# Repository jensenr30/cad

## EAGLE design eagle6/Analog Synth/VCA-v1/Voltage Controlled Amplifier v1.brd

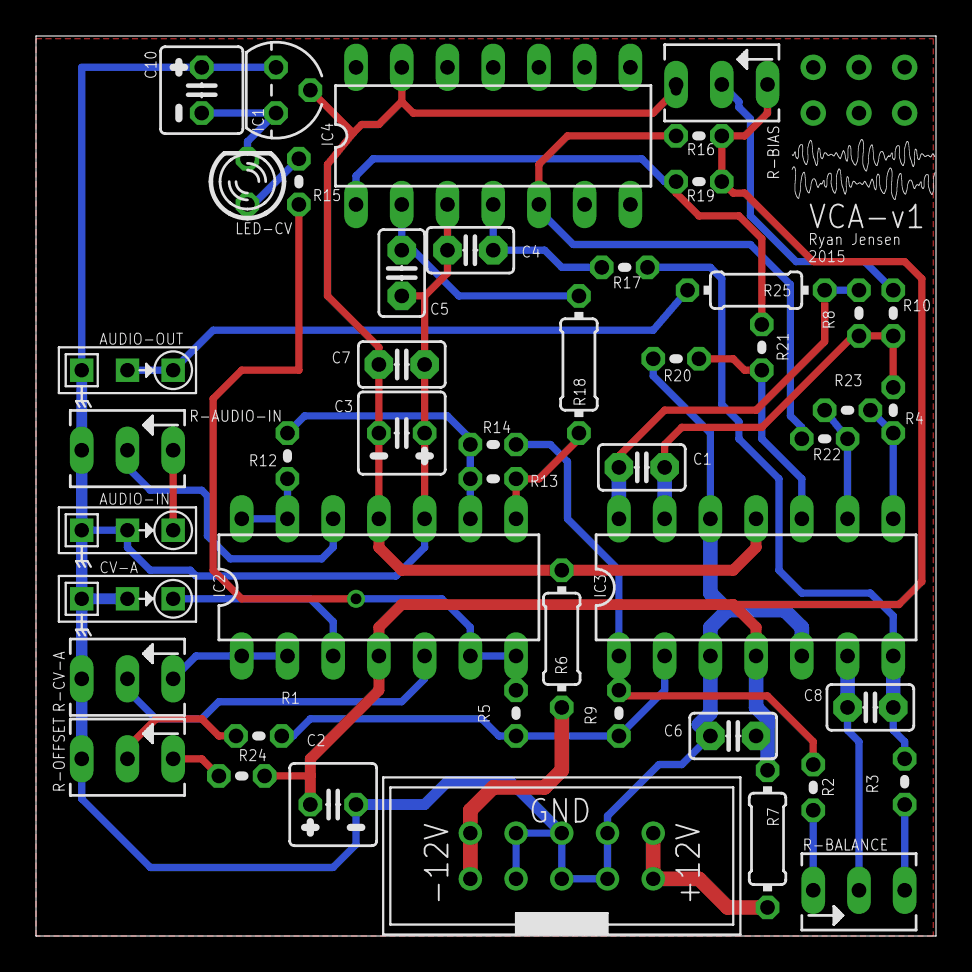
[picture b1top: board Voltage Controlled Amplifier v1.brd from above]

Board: 2 copper layers, 50.0 x 50.0 mm, 47 parts (0 on the bottom side), 35 nets.

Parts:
AUDIO-IN: I/O; MONO_JACK
AUDIO-OUT: I/O; MONO_JACK
C1, C8: 470p; C2.5-2
C2, C3: 100µ; C025-050X050
C4, C5: 390p; C2.5-2
C6, C7: 0.01µ; C2.5-2
C10: 10µ; C025-050X050
CV-A: I/O; MONO_JACK
IC1: 79L05; TO92
IC2, IC3: TL084P; DIL14
IC4: CA3046; DIL14
LED-CV: TLLG4400; LED3MM
R1, R2, R3, R5, R12, R20, R21, R22, R23: 100k; 0204V
R4, R13, R14: 1k; 0204V
R6, R7: 7.5; 0204/7
R8, R10, R15, R16, R17, R19: 10k; 0204V
R9: 33k; 0204V
R18: 10k; 0204/7
R24: 22k; 0204V
R25: 1k; 0204/7
R-AUDIO-IN: 100k Log; B64Y
R-BALANCE: 10k Trim; B64Y
R-BIAS: 100k Trim; B64Y
R-CV-A: 100k Log; B64Y
R-OFFSET: 10k Lin; B64Y
U$1: EURORACK-POWER

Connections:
+12V: C2.1, C6.1, IC2.4, IC3.4, R7.2, R16.2, R19.2, R24.2, R-BIAS.E
-5V: C10.2, IC1.3, LED-CV.K
-12V: C3.2, C7.2, IC1.2, IC2.11, IC3.11, IC4.13, R6.1, R-BIAS.A
GND: AUDIO-IN.P$1, AUDIO-IN.P$3, AUDIO-OUT.P$1, C2.2, C3.1, C4.1, C5.2, C6.2, C7.1, C10.1, CV-A.P$1, CV-A.P$3, IC1.1, IC2.10, IC3.3, IC3.5, IC3.12, IC4.3, R20.1, R-AUDIO-IN.A, R-CV-A.A, R-OFFSET.A, U$1.P$3, U$1.P$4, U$1.P$5, U$1.P$6, U$1.P$7, U$1.P$8
unnamed: IC2.6, IC2.7, R5.1, R15.2
unnamed: C4.2, IC4.4, R17.1
unnamed: CV-A.P$2, IC2.3
unnamed: IC2.1, IC2.2, R-CV-A.E
unnamed: R2.2, R-BALANCE.E
unnamed: IC3.2, R1.2, R5.2, R9.2
unnamed: R3.1, R-BALANCE.A
unnamed: R6.2, U$1.P$9, U$1.P$10
unnamed: AUDIO-IN.P$2, R-AUDIO-IN.E
unnamed: R7.1, U$1.P$1, U$1.P$2
unnamed: R10.1, R-BIAS.S
unnamed: LED-CV.A, R15.1
unnamed: R1.1, R-OFFSET.S
unnamed: IC2.5, R-CV-A.S
unnamed: IC3.1, R2.1, R9.1, R14.2
unnamed: IC2.13, IC2.14, R12.1
unnamed: IC2.12, R-AUDIO-IN.S
unnamed: C1.1, IC3.13, R4.2, R8.2, R10.2
unnamed: C5.1, IC4.2, R18.1
unnamed: IC2.9, R12.2, R13.1, R14.1
unnamed: C8.2, IC3.7, R3.2, R17.2
unnamed: IC4.5, R16.1, R22.1
unnamed: C8.1, IC3.6, R-BALANCE.S
unnamed: IC4.1, R19.1, R21.1
unnamed: IC2.8, R13.2, R18.2
unnamed: IC3.10, R20.2, R21.2
unnamed: IC3.9, R22.2, R23.1
unnamed: IC3.8, R4.1, R23.2
unnamed: AUDIO-OUT.P$2, AUDIO-OUT.P$3, R25.2
unnamed: C1.2, IC3.14, R8.1, R25.1
unnamed: R24.1, R-OFFSET.E
